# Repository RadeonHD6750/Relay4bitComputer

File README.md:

# Relay4bitComputer
릴레이로 만드는 4bit 컴퓨터

였느나 이왕하는거 8bit로 했다.

2026-05-25, 3-8디코더의 입력단LED 배치가 이상하게 되었으나 디코딩 기능 자체는 정상,
Enabler를 통하여 신호 전력 유지를 하려 했으나 의외로 없어도 잘 됨.
근데 있기는 해야 되는게 신호를 Enable/disable 해야 됨

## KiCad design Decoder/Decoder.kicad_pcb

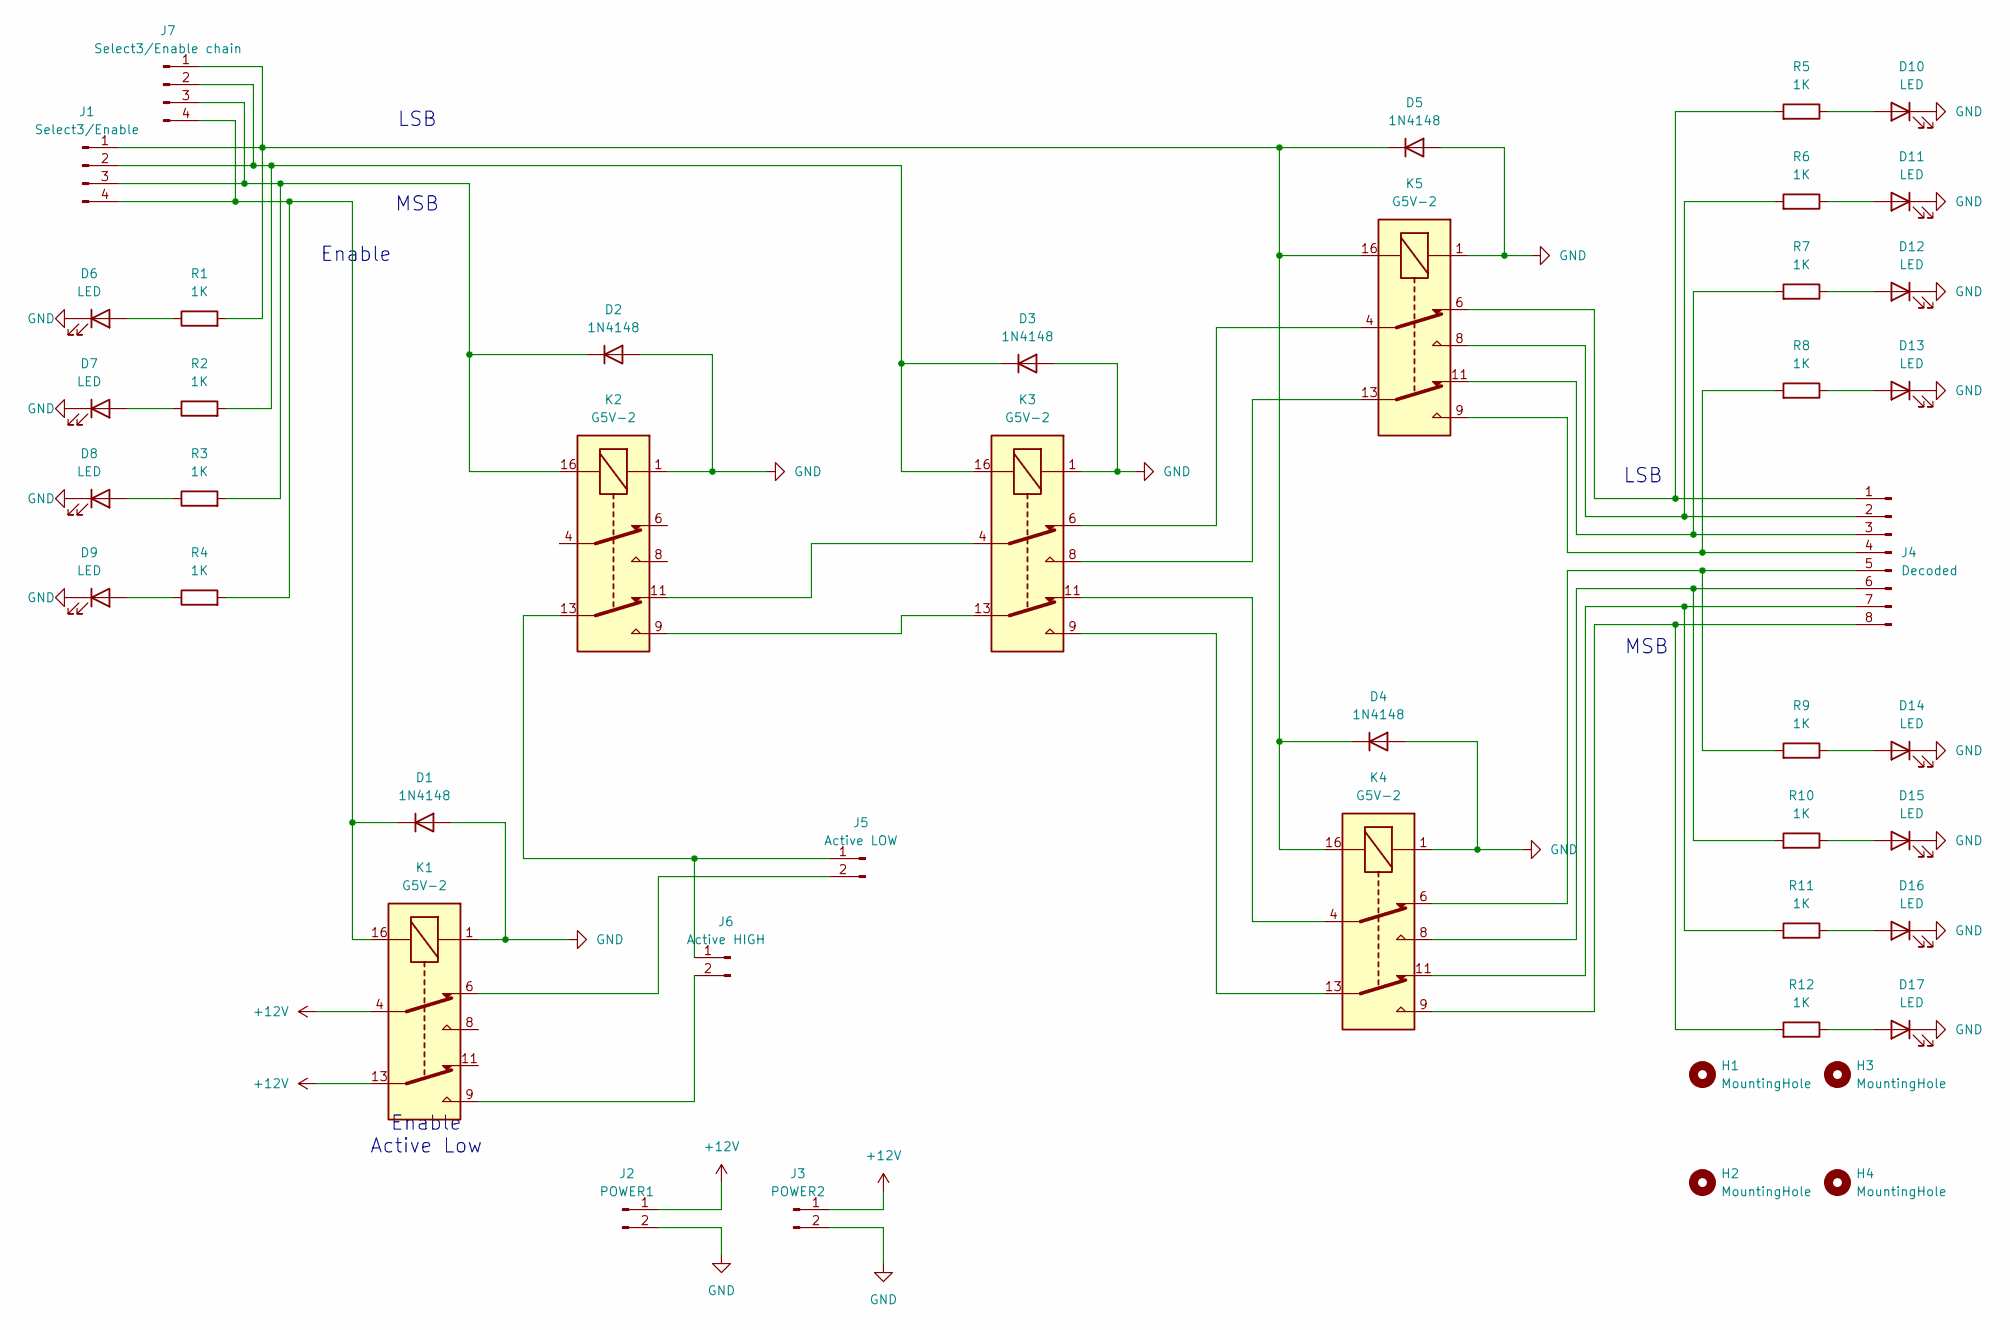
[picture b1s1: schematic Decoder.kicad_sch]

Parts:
D1, D2, D3, D4, D5: 1N4148; D_DO-35_SOD27_P7.62mm_Horizontal
D6, D7, D8, D9, D10, D11, D12, D13, D14, D15, D16, D17: LED; LED_D5.0mm
H1, H2, H3, H4: MountingHole; MountingHole_3.2mm_M3_Pad
J1: Select3/Enable; PinHeader_1x04_P2.54mm_Vertical
J2: POWER1; PinHeader_1x02_P2.54mm_Vertical
J3: POWER2; PinHeader_1x02_P2.54mm_Vertical
J4: Decoded; PinHeader_1x08_P2.54mm_Vertical
J5: Active LOW; PinHeader_1x02_P2.54mm_Vertical
J6: Active HIGH; PinHeader_1x02_P2.54mm_Vertical
J7: Select3/Enable chain; PinHeader_1x04_P2.54mm_Vertical
K1, K2, K3, K4, K5: G5V-2; Relay_DPDT_Omron_G5V-2
R1, R2, R3, R4, R5, R6, R7, R8, R9, R10, R11, R12: 1K; R_Axial_DIN0207_L6.3mm_D2.5mm_P10.16mm_Horizontal

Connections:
+12V: J2.1, J3.1, K1.4, K1.13
GND: D1.2 (A), D2.2 (A), D3.2 (A), D4.2 (A), D5.2 (A), D6.1 (K), D7.1 (K), D8.1 (K), D9.1 (K), D10.1 (K), D11.1 (K), D12.1 (K), D13.1 (K), D14.1 (K), D15.1 (K), D16.1 (K), D17.1 (K), J2.2, J3.2, K1.1, K2.1, K3.1, K4.1, K5.1
unnamed: D1.1 (K), J1.4, J7.4, K1.16, R4.2
unnamed: D2.1 (K), J1.3, J7.3, K2.16, R3.2
unnamed: D3.1 (K), J1.2, J7.2, K3.16, R2.2
unnamed: D4.1 (K), D5.1 (K), J1.1, J7.1, K4.16, K5.16, R1.2
unnamed: D6.2 (A), R1.1
unnamed: D7.2 (A), R2.1
unnamed: D8.2 (A), R3.1
unnamed: D9.2 (A), R4.1
unnamed: D10.2 (A), R5.1
unnamed: D11.2 (A), R6.1
unnamed: D12.2 (A), R7.1
unnamed: D13.2 (A), R8.1
unnamed: D14.2 (A), R9.1
unnamed: D15.2 (A), R10.1
unnamed: D16.2 (A), R11.1
unnamed: D17.2 (A), R12.1
unnamed: J4.1, K5.6, R5.2
unnamed: J4.2, K5.8, R6.2
unnamed: J4.3, K5.11, R7.2
unnamed: J4.4, K5.9, R8.2
unnamed: J4.5, K4.6, R9.2
unnamed: J4.6, K4.8, R10.2
unnamed: J4.7, K4.11, R11.2
unnamed: J4.8, K4.9, R12.2
unnamed: J5.1, J6.1, K2.13
unnamed: J5.2, K1.6
unnamed: J6.2, K1.9
unnamed: K2.9, K3.13
unnamed: K2.11, K3.4
unnamed: K3.6, K5.4
unnamed: K3.8, K5.13
unnamed: K3.9, K4.13
unnamed: K3.11, K4.4

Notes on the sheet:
LSB
MSB
Enable
Enable Active Low

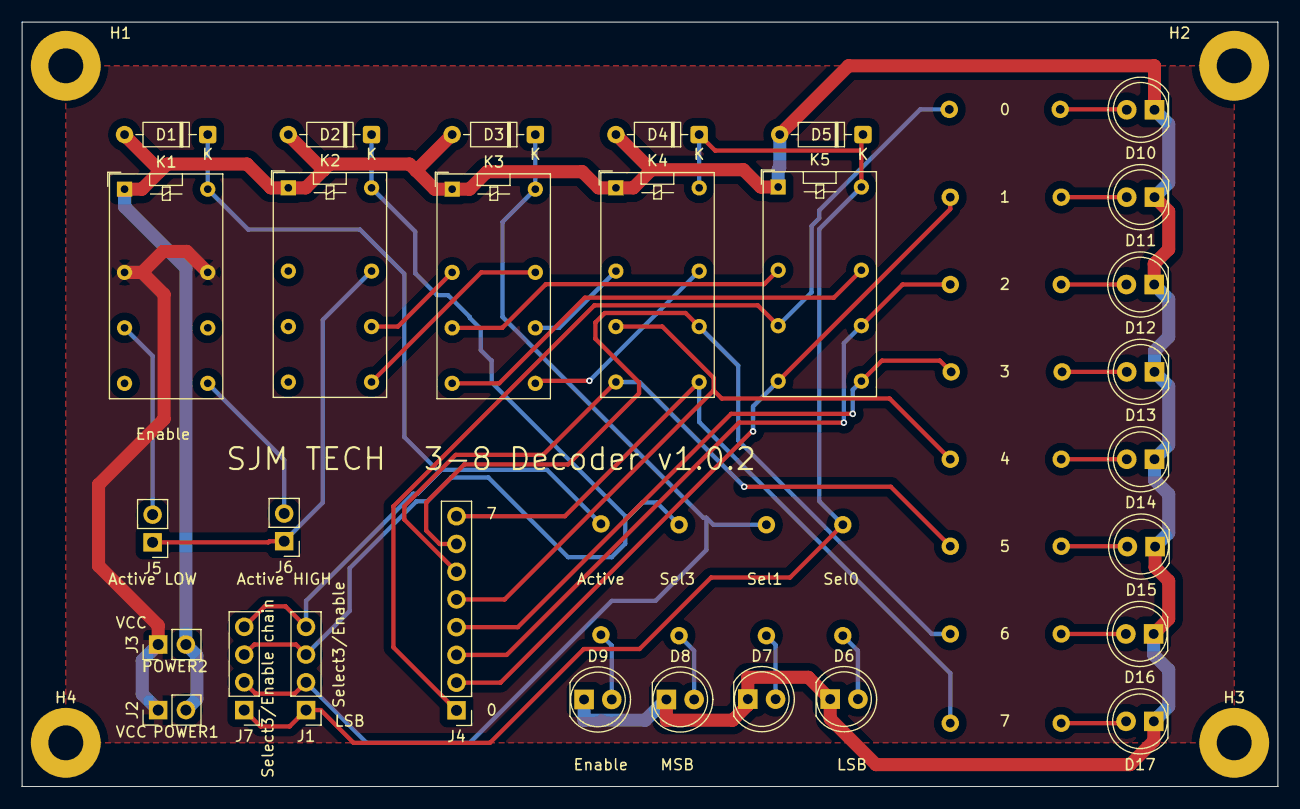
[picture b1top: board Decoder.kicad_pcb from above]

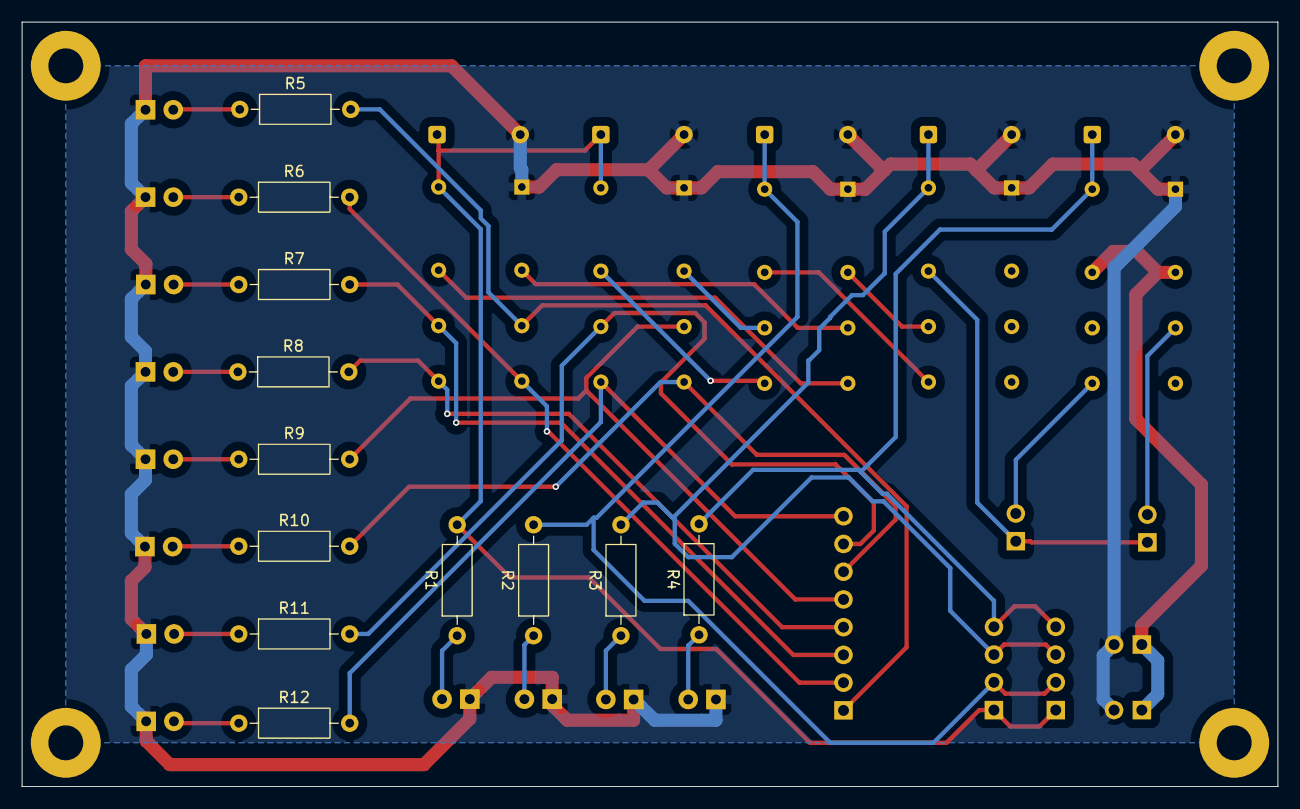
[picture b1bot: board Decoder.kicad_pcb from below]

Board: 2 copper layers, 115.0 x 70.0 mm, 45 parts (12 on the bottom side), 35 nets.

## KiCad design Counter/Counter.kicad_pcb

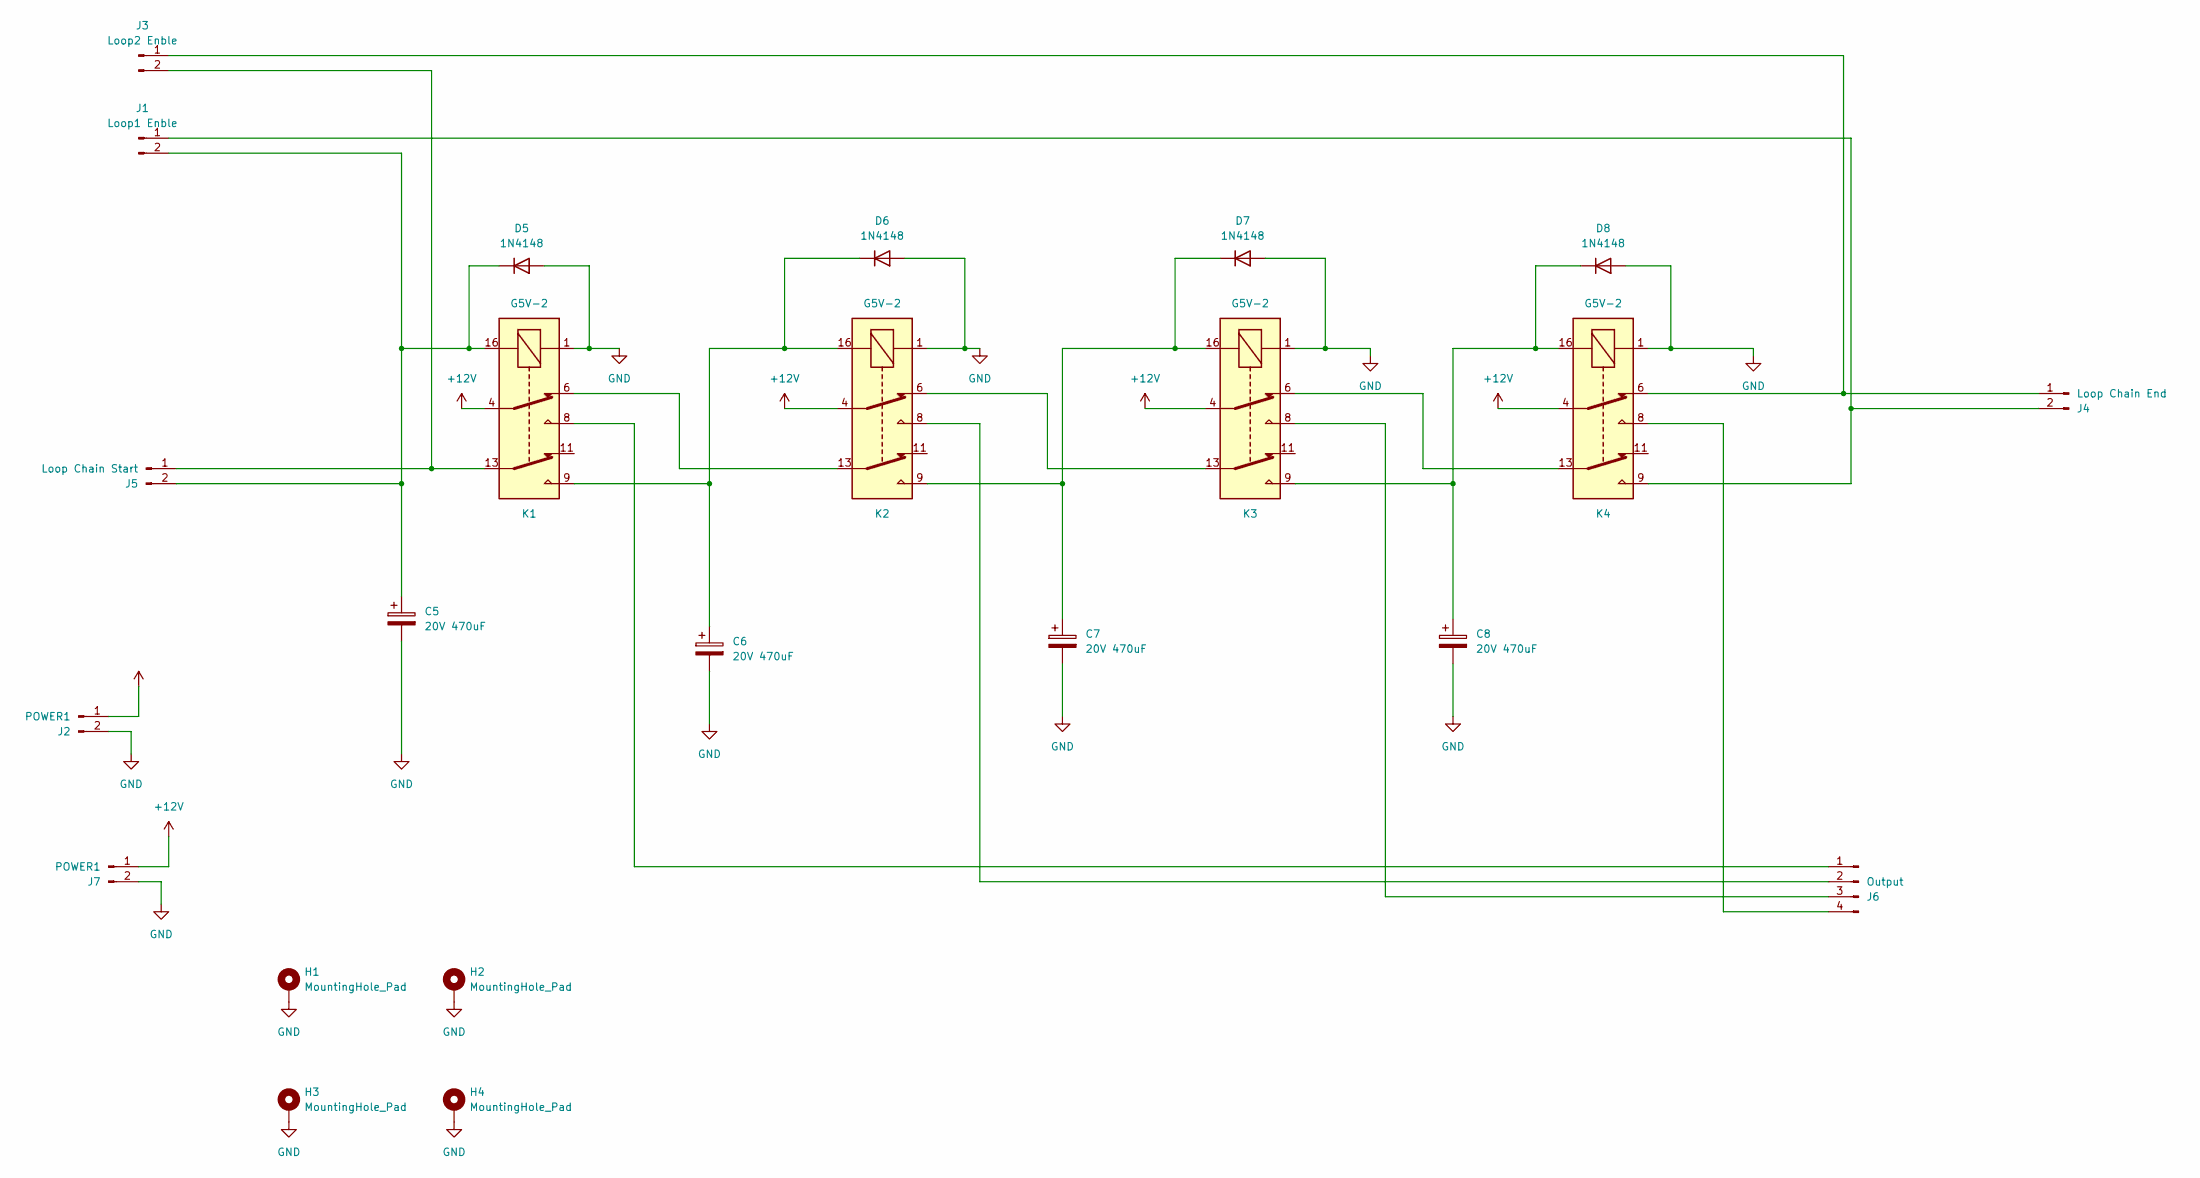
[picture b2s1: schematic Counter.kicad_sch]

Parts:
C5, C6, C7, C8: 20V 470uF; CP_Radial_D12.5mm_P5.00mm
D5, D6, D7, D8: 1N4148; D_DO-35_SOD27_P7.62mm_Horizontal
H1, H2, H3, H4: MountingHole_Pad; MountingHole_3.2mm_M3_Pad
J1: Loop1 Enble; PinHeader_1x02_P2.54mm_Vertical
J2, J7: POWER1; PinHeader_1x02_P2.54mm_Vertical
J3: Loop2 Enble; PinHeader_1x02_P2.54mm_Vertical
J4: Loop Chain End; PinHeader_1x02_P2.54mm_Vertical
J5: Loop Chain Start; PinHeader_1x02_P2.54mm_Vertical
J6: Output; PinHeader_1x04_P2.54mm_Vertical
K1, K2, K3, K4: G5V-2; Relay_DPDT_Omron_G5V-2

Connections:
+12V: J2.1, J7.1, K1.4, K2.4, K3.4, K4.4
GND: C5.2, C6.2, C7.2, C8.2, D5.2 (A), D6.2 (A), D7.2 (A), D8.2 (A), H1.1, H2.1, H3.1, H4.1, J2.2, J7.2, K1.1, K2.1, K3.1, K4.1
unnamed: C5.1, D5.1 (K), J1.2, J5.2, K1.16
unnamed: C6.1, D6.1 (K), K1.9, K2.16
unnamed: C7.1, D7.1 (K), K2.9, K3.16
unnamed: C8.1, D8.1 (K), K3.9, K4.16
unnamed: J1.1, J4.2, K4.9
unnamed: J3.1, J4.1, K4.6
unnamed: J3.2, J5.1, K1.13
unnamed: J6.1, K1.8
unnamed: J6.2, K2.8
unnamed: J6.3, K3.8
unnamed: J6.4, K4.8
unnamed: K1.6, K2.13
unnamed: K2.6, K3.13
unnamed: K3.6, K4.13

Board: 2 copper layers, 23 parts (0 on the bottom side), 16 nets, no tracks yet.

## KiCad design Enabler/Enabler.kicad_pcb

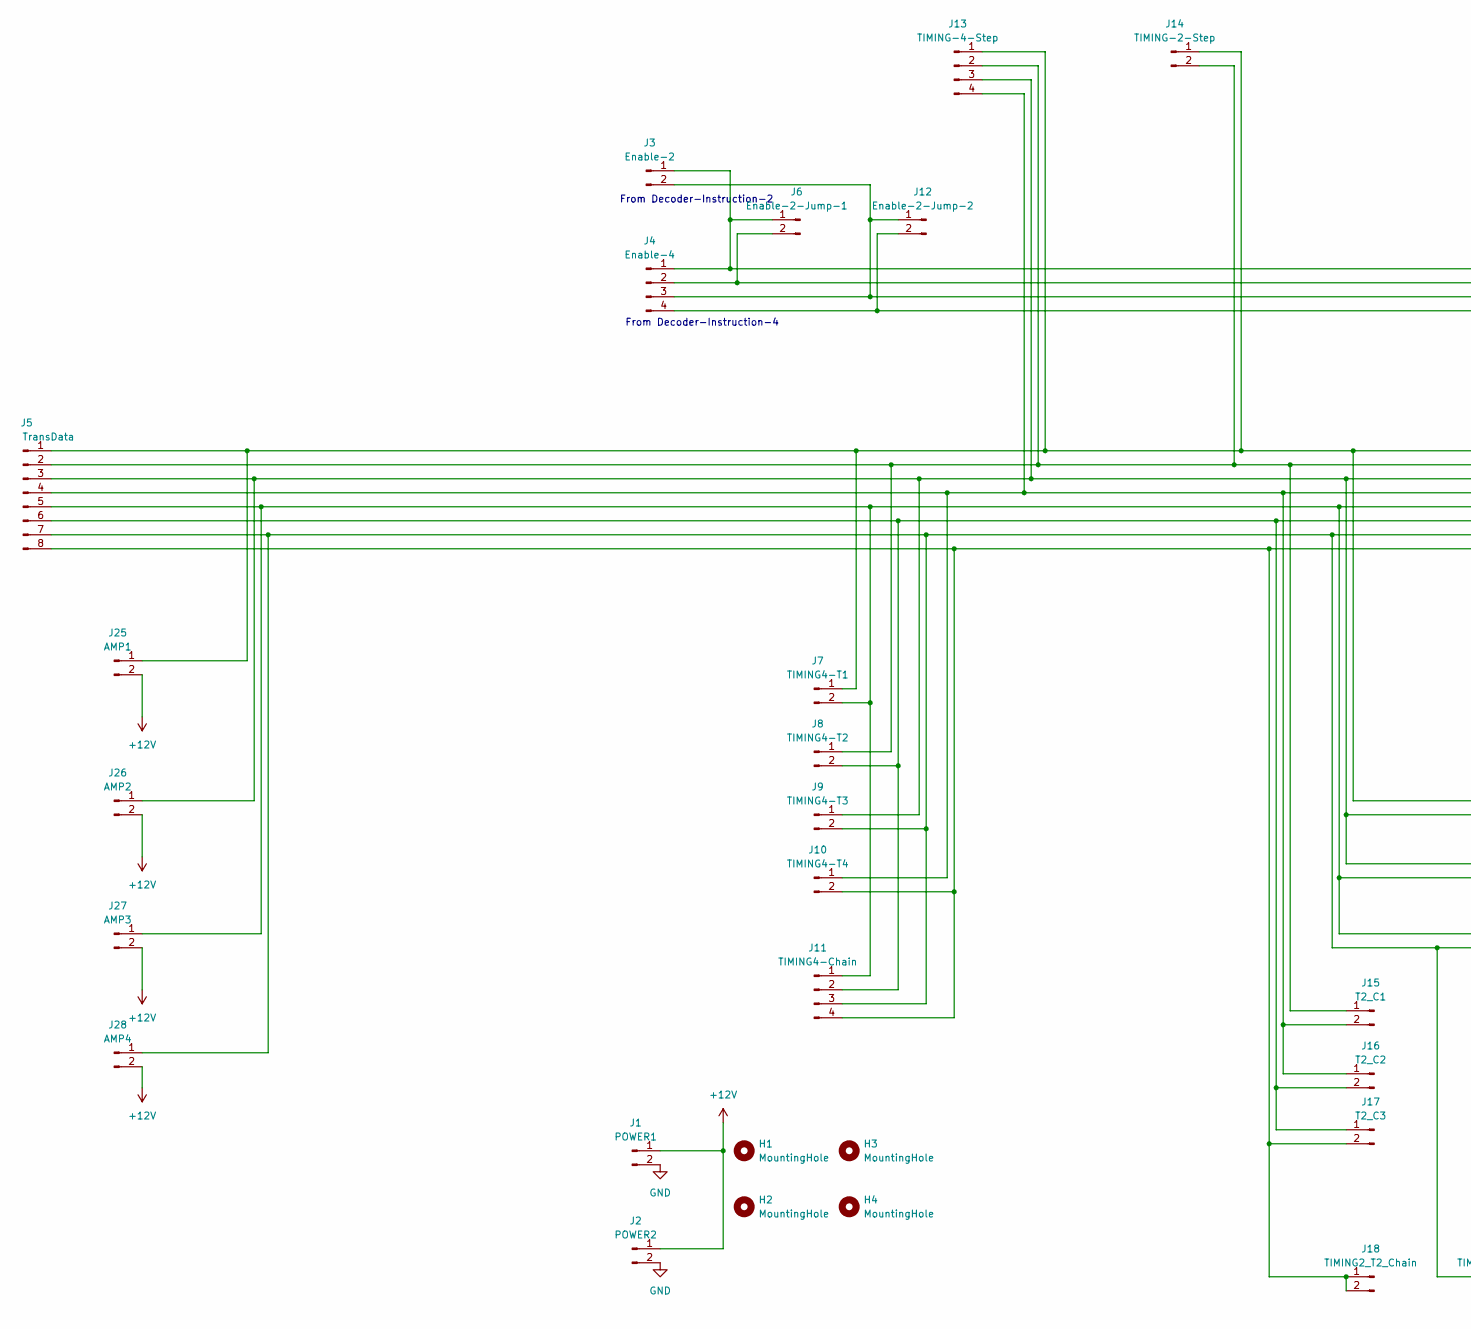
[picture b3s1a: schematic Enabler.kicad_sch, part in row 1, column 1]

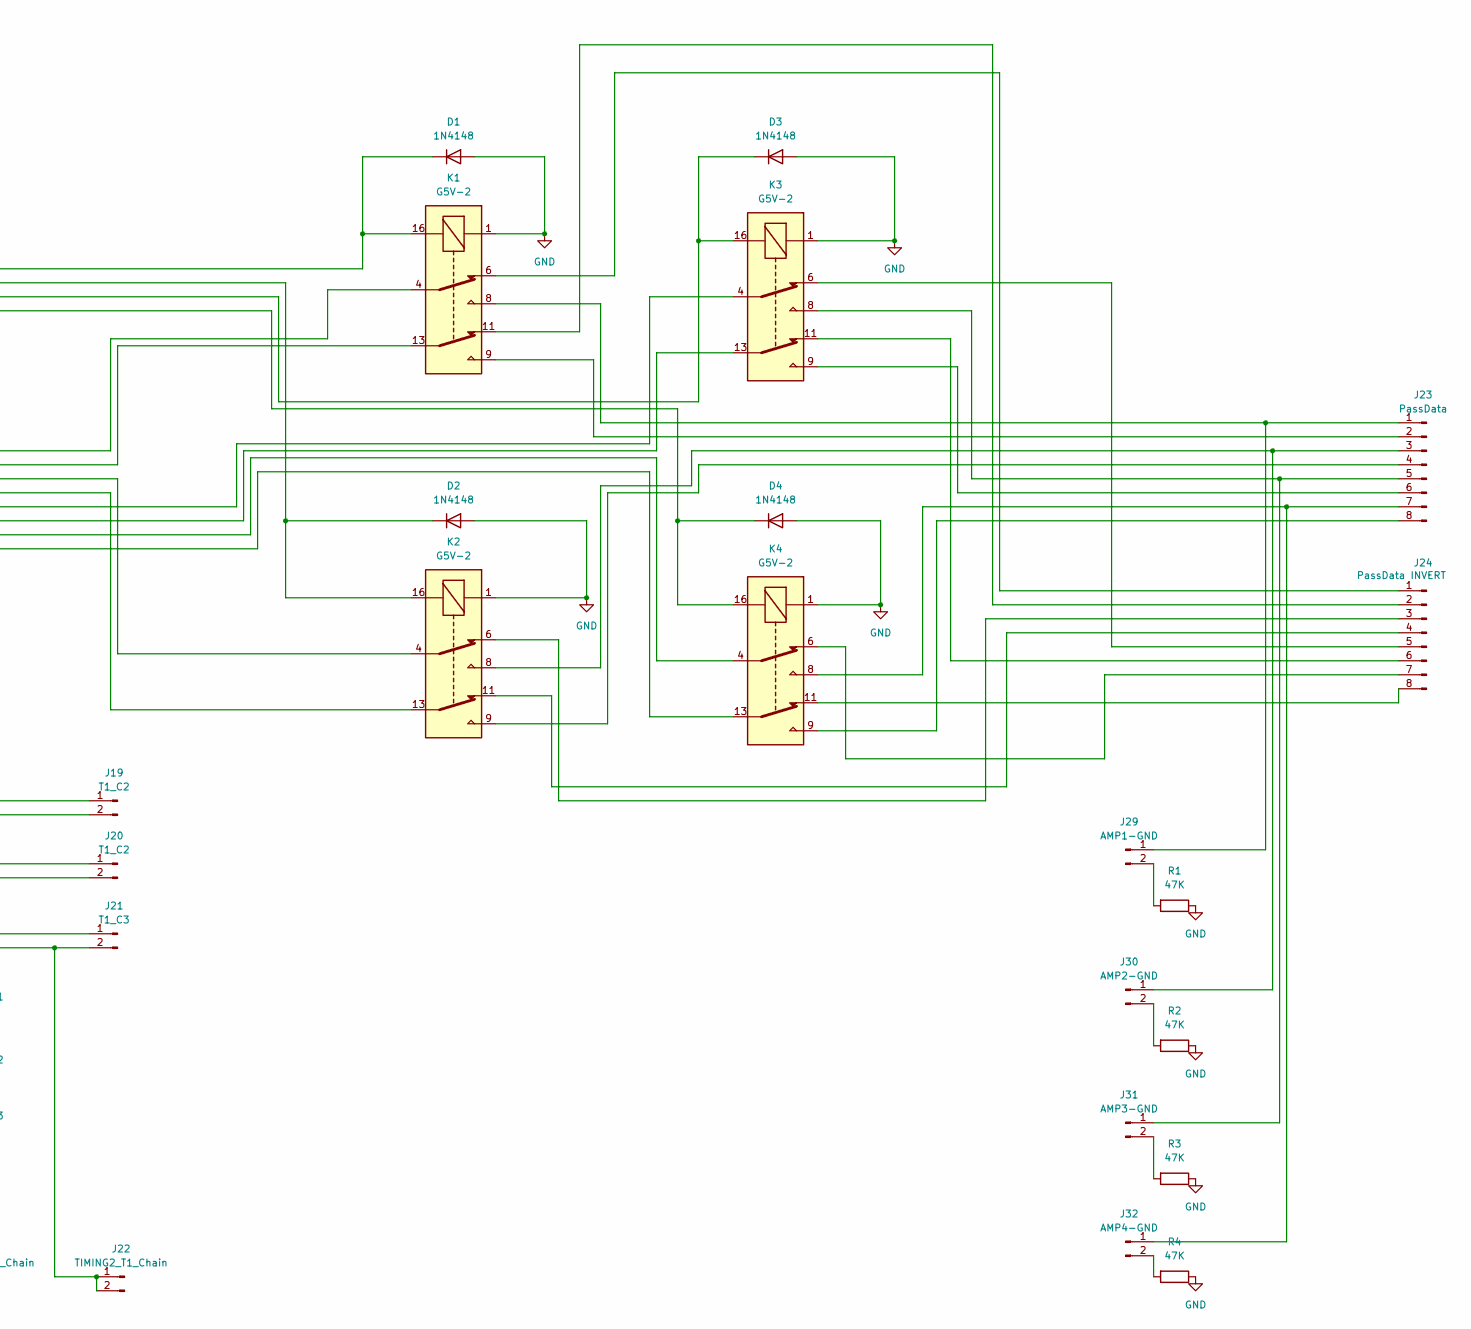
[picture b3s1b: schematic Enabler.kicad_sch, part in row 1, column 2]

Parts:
D1, D2, D3, D4: 1N4148; D_DO-35_SOD27_P7.62mm_Horizontal
H1, H2, H3, H4: MountingHole; MountingHole_3.2mm_M3
J1: POWER1; PinHeader_1x02_P2.54mm_Vertical
J2: POWER2; PinHeader_1x02_P2.54mm_Vertical
J3: Enable-2; PinHeader_1x02_P2.54mm_Vertical
J4: Enable-4; PinHeader_1x04_P2.54mm_Vertical
J5: TransData; PinHeader_1x08_P2.54mm_Vertical
J6: Enable-2-Jump-1; PinHeader_1x02_P2.54mm_Vertical
J7: TIMING4-T1; PinHeader_1x02_P2.54mm_Vertical
J8: TIMING4-T2; PinHeader_1x02_P2.54mm_Vertical
J9: TIMING4-T3; PinHeader_1x02_P2.54mm_Vertical
J10: TIMING4-T4; PinHeader_1x02_P2.54mm_Vertical
J11: TIMING4-Chain; PinHeader_1x04_P2.54mm_Vertical
J12: Enable-2-Jump-2; PinHeader_1x02_P2.54mm_Vertical
J13: TIMING-4-Step; PinHeader_1x04_P2.54mm_Vertical
J14: TIMING-2-Step; PinHeader_1x02_P2.54mm_Vertical
J15: T2_C1; PinHeader_1x02_P2.54mm_Vertical
J16: T2_C2; PinHeader_1x02_P2.54mm_Vertical
J17: T2_C3; PinHeader_1x02_P2.54mm_Vertical
J18: TIMING2_T2_Chain; PinHeader_1x02_P2.54mm_Vertical
J19, J20: T1_C2; PinHeader_1x02_P2.54mm_Vertical
J21: T1_C3; PinHeader_1x02_P2.54mm_Vertical
J22: TIMING2_T1_Chain; PinHeader_1x02_P2.54mm_Vertical
J23: PassData; PinHeader_1x08_P2.54mm_Vertical
J24: PassData INVERT; PinHeader_1x08_P2.54mm_Vertical
J25: AMP1; PinHeader_1x02_P2.54mm_Vertical
J26: AMP2; PinHeader_1x02_P2.54mm_Vertical
J27: AMP3; PinHeader_1x02_P2.54mm_Vertical
J28: AMP4; PinHeader_1x02_P2.54mm_Vertical
J29: AMP1-GND; PinHeader_1x02_P2.54mm_Vertical
J30: AMP2-GND; PinHeader_1x02_P2.54mm_Vertical
J31: AMP3-GND; PinHeader_1x02_P2.54mm_Vertical
J32: AMP4-GND; PinHeader_1x02_P2.54mm_Vertical
K1, K2, K3, K4: G5V-2; Relay_DPDT_Omron_G5V-2
R1, R2, R3, R4: 47K; R_Axial_DIN0207_L6.3mm_D2.5mm_P10.16mm_Horizontal

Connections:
+12V: J1.1, J2.1, J25.2, J26.2, J27.2, J28.2
GND: D1.2 (A), D2.2 (A), D3.2 (A), D4.2 (A), J1.2, J2.2, K1.1, K2.1, K3.1, K4.1, R1.1, R2.1, R3.1, R4.1
unnamed: D1.1 (K), J3.1, J4.1, J6.1, K1.16
unnamed: D2.1 (K), J4.2, J6.2, K2.16
unnamed: D3.1 (K), J3.2, J4.3, J12.1, K3.16
unnamed: D4.1 (K), J4.4, J12.2, K4.16
unnamed: J5.4, J10.1, J13.4, J15.2, J16.1, K2.13
unnamed: J5.8, J10.2, J11.4, J17.2, J18.1, J18.2, K4.13
unnamed: J5.5, J7.2, J11.1, J20.2, J21.1, J27.1, K3.4
unnamed: J5.6, J8.2, J11.2, J16.2, J17.1, K3.13
unnamed: J5.7, J9.2, J11.3, J21.2, J22.1, J22.2, J28.1, K4.4
unnamed: J5.1, J7.1, J13.1, J14.1, J19.1, J25.1, K1.4
unnamed: J5.2, J8.1, J13.2, J14.2, J15.1, K1.13
unnamed: J5.3, J9.1, J13.3, J19.2, J20.1, J26.1, K2.4
unnamed: J23.1, J29.1, K1.8
unnamed: J23.2, K1.9
unnamed: J23.3, J30.1, K2.8
unnamed: J23.4, K2.9
unnamed: J23.5, J31.1, K3.8
unnamed: J23.6, K3.9
unnamed: J23.7, J32.1, K4.8
unnamed: J23.8, K4.9
unnamed: J24.1, K1.6
unnamed: J24.2, K1.11
unnamed: J24.3, K2.6
unnamed: J24.4, K2.11
unnamed: J24.5, K3.6
unnamed: J24.6, K3.11
unnamed: J24.7, K4.6
unnamed: J24.8, K4.11
unnamed: J29.2, R1.2
unnamed: J30.2, R2.2
unnamed: J31.2, R3.2
unnamed: J32.2, R4.2

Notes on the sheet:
From Decoder-Instruction-4
From Decoder-Instruction-2

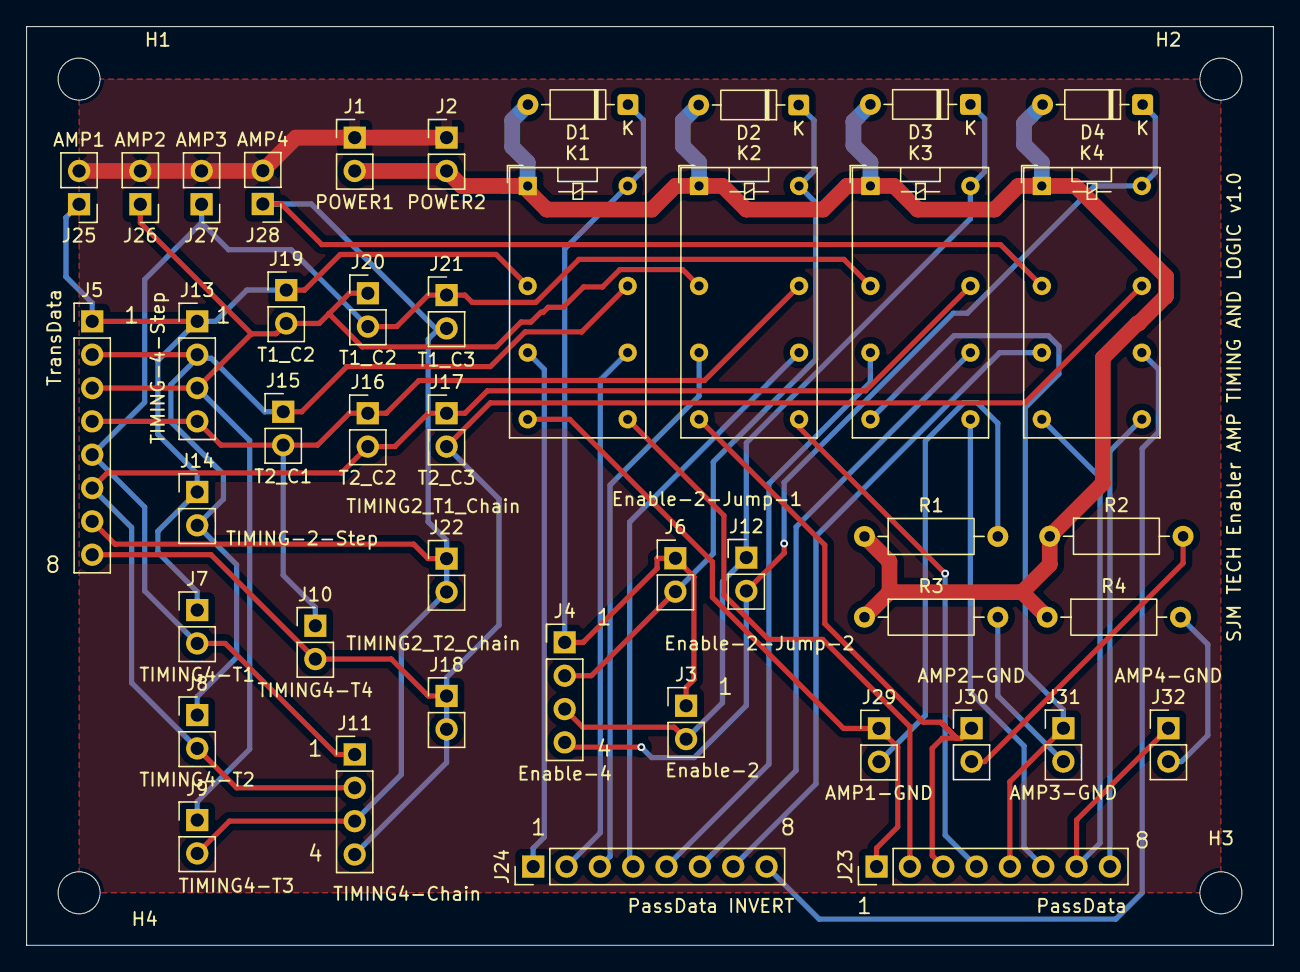
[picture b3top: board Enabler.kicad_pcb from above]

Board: 2 copper layers, 95.0 x 70.0 mm, 48 parts (0 on the bottom side), 34 nets.
